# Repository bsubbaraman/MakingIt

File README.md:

# MakingIt
documentation for HCDE 548 Making It: Research Through Digital Design and Fabrication

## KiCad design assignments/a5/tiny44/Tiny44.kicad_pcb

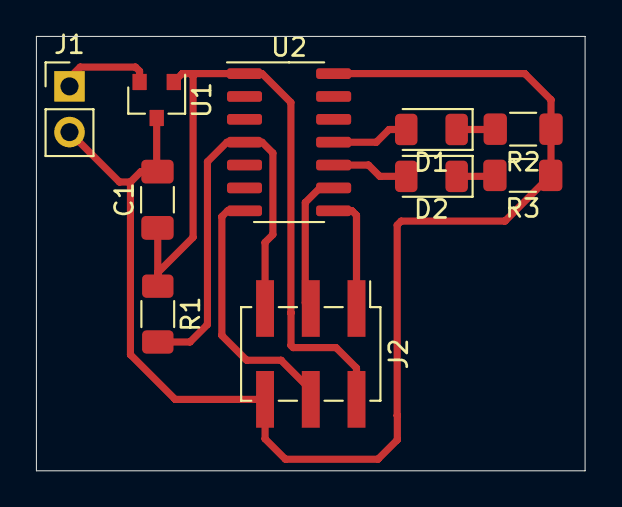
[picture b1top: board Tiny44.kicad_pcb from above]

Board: 2 copper layers, 30.5 x 24.1 mm, 10 parts (0 on the bottom side), 11 nets.

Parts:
C1: 1uF; C_1206_3216Metric_Pad1.33x1.80mm_HandSolder
D1, D2: LED; LED_1206_3216Metric
J1: Conn_01x02_Male; PinHeader_1x02_P2.54mm_Vertical
J2: AVR-ISP-6; PinHeader_2x03_P2.54mm_Vertical_SMD
R1: 10k; R_1206_3216Metric_Pad1.30x1.75mm_HandSolder
R2, R3: 1k; R_1206_3216Metric_Pad1.30x1.75mm_HandSolder
U1: LM3480-5.0; SOT-23
U2: ATtiny44A-SSU; SOIC-14_3.9x8.7mm_P1.27mm

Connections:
+9V: J1.1, U1.2
/MISO: J2.1, U2.8
/MOSI: J2.4, U2.7
/RESET: J2.5, R1.2, U2.4
/SCK: J2.3, U2.9
GND: C1.2, J1.2, J2.6, R2.1, R3.1, U1.3, U2.14
unnamed: D1.1, R2.2
unnamed: D1.2, U2.11
unnamed: D2.1, R3.2
unnamed: D2.2, U2.10
VCC: C1.1, J2.2, R1.1, U1.1, U2.1

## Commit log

2021-10-01 initial setup
2021-10-07 shoes
2021-10-21 typo
2021-10-21 typo pt 2
2021-10-28 a4 part1
2021-10-28 a4 pt 2
2021-11-08 change weekly title
2021-11-15 desinging pcbs
2021-11-16 fix image path
2021-11-16 change image path
2021-11-24 a7, this time with smaller files
2021-11-29 a7 pt 2
2021-12-09 final
2021-12-09 final project docs
2021-12-09 fix typo!
2021-12-09 typo fix
